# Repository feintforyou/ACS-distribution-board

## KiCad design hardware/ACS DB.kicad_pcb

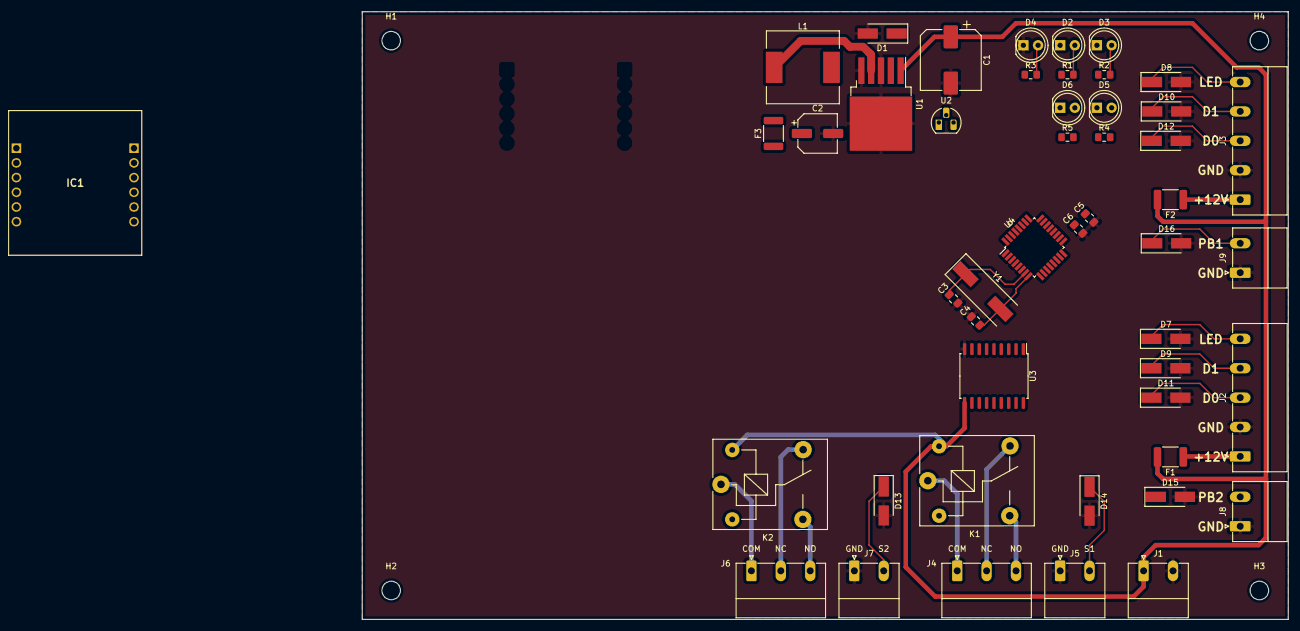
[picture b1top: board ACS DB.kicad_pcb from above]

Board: 2 copper layers, 160.0 x 105.0 mm, 52 parts (0 on the bottom side), 36 nets.

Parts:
C1: 470uF/25V; CP_Elec_10x10
C2: 220uF/15V; CP_Elec_6.3x7.7
C3: 22pF; C_0805_2012Metric_Pad1.18x1.45mm_HandSolder
C4, C6: 100nF; C_0805_2012Metric_Pad1.18x1.45mm_HandSolder
C5: 10uF; C_0805_2012Metric_Pad1.18x1.45mm_HandSolder
D1: SS34; D_SMA_Handsoldering
D2: LED_Activity; LED_D5.0mm
D3: LED_Input; LED_D5.0mm
D4: LED_Power; LED_D5.0mm
D5: LED_Door1; LED_D5.0mm
D6: LED_Door2; LED_D5.0mm
D7, D8, D9, D10, D11, D12, D13, D14, D15, D16: D_TVS; D_SMA_Handsoldering
F1, F2: Polyfuse; R_1812_4532Metric_Pad1.30x3.40mm_HandSolder
F3: MF-MSMF250/X; R_1812_4532Metric_Pad1.30x3.40mm_HandSolder
H1, H2, H3, H4: MountingHole; MountingHole_3.2mm_M3
IC1: USR-ES1; USRES1
J1: Power; PhoenixContact_MC_1,5_2-G-5.08_1x02_P5.08mm_Horizontal
J2: Reader 2; PhoenixContact_MC_1,5_5-G-5.08_1x05_P5.08mm_Horizontal
J3: Reader 1; PhoenixContact_MC_1,5_5-G-5.08_1x05_P5.08mm_Horizontal
J4: Relay 1; PhoenixContact_MC_1,5_3-G-5.08_1x03_P5.08mm_Horizontal
J5: Sensor 1; PhoenixContact_MC_1,5_2-G-5.08_1x02_P5.08mm_Horizontal
J6: Relay 2; PhoenixContact_MC_1,5_3-G-5.08_1x03_P5.08mm_Horizontal
J7: Sensor 2; PhoenixContact_MC_1,5_2-G-5.08_1x02_P5.08mm_Horizontal
J8: PB2; PhoenixContact_MC_1,5_2-G-5.08_1x02_P5.08mm_Horizontal
J9: PB1; PhoenixContact_MC_1,5_2-G-5.08_1x02_P5.08mm_Horizontal
K1, K2: SANYOU_SRD_Form_C; Relay_SPDT_SANYOU_SRD_Series_Form_C
L1: 68uH; L_12x12mm_H6mm
R1, R2, R3, R4, R5: R; R_0805_2012Metric_Pad1.15x1.40mm_HandSolder
U1: LM2596S-5; TO-263-5_TabPin3
U2: LM35-LP; TO-92_HandSolder
U3: ULN2803A; SOIC-18W_7.5x11.6mm_P1.27mm
U4: ATmega328P-AU; TQFP-32_7x7mm_P0.8mm
Y1: Crystal; Crystal_SMD_HC49-SD

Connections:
+5V: C2.1, C5.1, C6.1, L1.1, R1.1, R2.1, R4.1, R5.1, U1.4, U2.1, U4.4, U4.6, U4.18, U4.20
+12V: C1.1, F1.2, F2.2, J1.1, K1.5, K2.5, R3.1, U1.1, U3.10
/COM_1: J4.1, K1.1
/COM_2: J6.1, K2.1
/D0_1: D12.1, J3.3, U4.32
/D0_2: D11.1, J2.3, U4.2
/D1_1: D10.1, J3.4, U4.1
/D1_2: D9.1, J2.4, U4.9
/Door1: U3.1, U4.23
/Door2: U3.2, U4.25
/LED_1: D8.1, J3.5, U4.12
/LED_2: D7.1, J2.5, U4.13
/LED_ACT: D2.1, U4.16
/LED_IN: D3.1, U4.17
/LM35: U2.2, U4.19
/NC_1: J4.2, K1.4
/NC_2: J6.2, K2.4
/NO_1: J4.3, K1.3
/NO_2: J6.3, K2.3
/O1: K1.2, U3.18
/O2: K2.2, U3.17
/PB1: D16.1, J9.2, U4.10
/PB2: D15.1, J8.2, U4.11
/S1: D5.1, D14.1, J5.2, U4.24
/S2: D6.1, D13.1, J7.2, U4.26
/XTAL1: C3.1, U4.7, Y1.1
/XTAL2: C4.1, U4.8, Y1.2
GND: C1.2, C2.2, C3.2, C4.2, C5.2, C6.2, D1.2, D4.1, D7.2, D8.2, D9.2, D10.2, D11.2, D12.2, D13.2, D14.2, D15.2, D16.2, J1.2, J2.2, J3.2, J5.1, J7.1, J8.1, J9.1, U1.3, U1.5, U3.9, U4.3, U4.5, U4.21
unnamed: D1.1, L1.2, U1.2
unnamed: D2.2, R1.2
unnamed: D3.2, R2.2
unnamed: D4.2, R3.2
unnamed: D5.2, R4.2
unnamed: D6.2, R5.2
unnamed: F1.1, J2.1
unnamed: F2.1, J3.1

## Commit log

2021-08-30 update pcb layout
2021-09-03 chore : add library as submodule
2021-09-03 add library package
